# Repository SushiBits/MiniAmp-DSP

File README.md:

# MiniAmp DSP

Miniature Audio Amplifier with a DSP inside.

eUPID: `M2AUv3-AMP4268`

## Specifications

* Power input: DC 9-24V 6W, center positive barrel jack.
* Signal input: Unbalanced consumer line level, 3.5mm TRS jack.
* Outputs:
  * Left and Right speakers: balanced 6W class D output, screw terminals.
  * Center speaker: balanced 1W class AB output, screw terminals.
  * Subwoofer: Consumer line level, RCA coaxial.
  * Headphone: Unbalanced 6W class D output, 3.5mm TRS jack. The prescense of a
    headphone disables all other outputs.
* DSP: Analog Devices AD1701 SigmaDSP.

## Programming the DSP

This DSP is programmed using [Analog Devices SigmaStudio][1]. You need a USBi,
for example the [SigmaLink USBi][2], to program the devce.

[1]: https://www.analog.com/en/design-center/evaluation-hardware-and-software/software/ss_sigst_02.html
[2]: https://github.com/freeDSP/SigmaLink-USBi

## License & Contacts

Copyright &copy; 2019-2020 Max Chan. All rights reserved.

This project is licensed under [3-clause BSD license](LICENSE.md).

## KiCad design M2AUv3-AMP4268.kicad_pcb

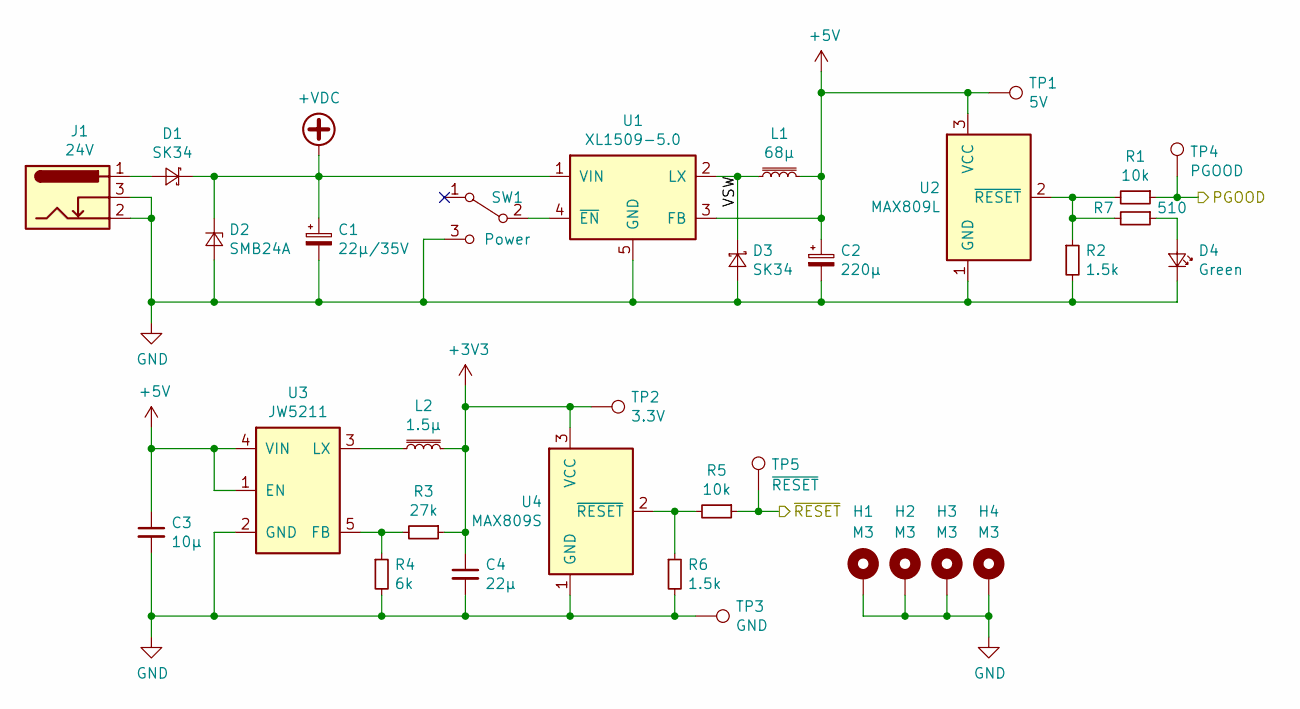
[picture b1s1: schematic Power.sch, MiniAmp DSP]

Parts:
C1: 22µ/35V; CP_Elec_6.3x5.4
C2: 220µ; CP_Elec_6.3x5.4
C3: 10µ; C_0805_2012Metric_Pad1.15x1.40mm_HandSolder
C4: 22µ; C_0805_2012Metric_Pad1.15x1.40mm_HandSolder
D1, D3: SK34; D_SMB
D2: SMB24A; D_SMB
D4: Green; LED_1206_3216Metric_Pad1.42x1.75mm_HandSolder
H1, H2, H3, H4: M3; MountingHole_3.2mm_M3_Pad_Via
J1: 24V; BarrelJack_Wuerth_6941xx301002
L1: 68µ; L_Taiyo-Yuden_NR-60xx_HandSoldering
L2: 1.5µ; L_0806_2016Metric_Pad1.15x1.80mm_HandSolder
R1, R5: 10k; R_0603_1608Metric_Pad1.05x0.95mm_HandSolder
R2, R6: 1.5k; R_0603_1608Metric_Pad1.05x0.95mm_HandSolder
R3: 27k; R_0603_1608Metric_Pad1.05x0.95mm_HandSolder
R4: 6k; R_0603_1608Metric_Pad1.05x0.95mm_HandSolder
R7: 510; R_0603_1608Metric_Pad1.05x0.95mm_HandSolder
SW1: Power; SW_SPDT_PCM12
TP1: 5V; TestPoint_Loop_D2.54mm_Drill1.5mm_Beaded
TP2: 3.3V; TestPoint_Loop_D2.54mm_Drill1.5mm_Beaded
TP3: GND; TestPoint_Loop_D2.54mm_Drill1.5mm_Beaded
TP4: PGOOD; TestPoint_Loop_D2.54mm_Drill1.5mm_Beaded
TP5: ~RESET; TestPoint_Loop_D2.54mm_Drill1.5mm_Beaded
U1: XL1509-5.0; SOIC-8_3.9x4.9mm_P1.27mm
U2: MAX809L; SOT-23
U3: JW5211; SOT-23-5
U4: MAX809S; SOT-23

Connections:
+3V3: C4.1, L2.2, R3.1, TP2.1, U4.3 (VCC); also elsewhere on the board
+5V: C2.1, C3.1, L1.2, TP1.1, U1.3 (FB), U2.3 (VCC), U3.1 (EN), U3.4 (VIN); also elsewhere on the board
+VDC: C1.1, D1.1 (K), D2.1 (K), U1.1 (VIN)
/DSP/~RESET: R5.1, TP5.1; also elsewhere on the board
/PGOOD: R1.1, TP4.1; also elsewhere on the board
/Power Delivery/VSW: D3.1 (K), L1.1, U1.2 (LX)
GND: C1.2, C2.2, C3.2, C4.2, D2.2 (A), D3.2 (A), D4.1 (K), H1.1, H2.1, H3.1, H4.1, J1.2, J1.3, R2.2, R4.2, R6.2, SW1.3 (C), TP3.1, U1.5 (GND), U1.6 (GND), U1.7 (GND), U1.8 (GND), U2.1 (GND), U3.2 (GND), U4.1 (GND); also elsewhere on the board
unnamed: D1.2 (A), J1.1
unnamed: D4.2 (A), R7.1
unnamed: L2.1, U3.3 (LX)
unnamed: R1.2, R2.1, R7.2, U2.2 (~RESET~)
unnamed: R3.2, R4.1, U3.5 (FB)
unnamed: R5.2, R6.1, U4.2 (~RESET~)
unnamed: SW1.2 (B), U1.4 (~EN)

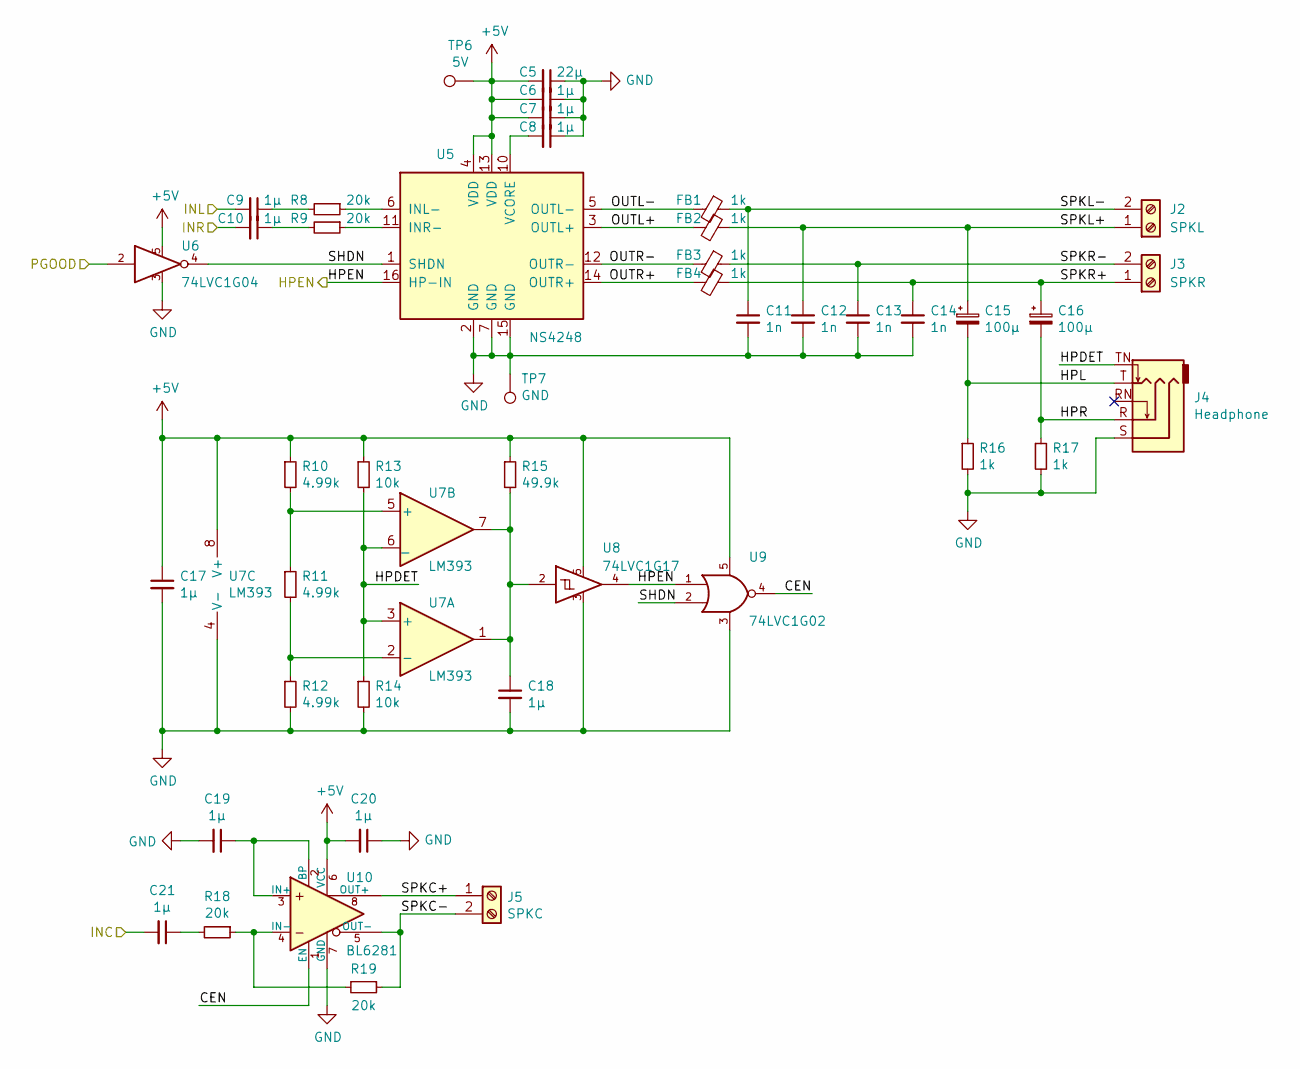
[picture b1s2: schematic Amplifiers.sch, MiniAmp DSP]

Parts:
C5: 22µ; C_0805_2012Metric_Pad1.15x1.40mm_HandSolder
C6, C7, C8, C9, C10, C17, C18, C19, C20, C21: 1µ; C_0603_1608Metric_Pad1.05x0.95mm_HandSolder
C11, C12, C13, C14: 1n; C_0603_1608Metric_Pad1.05x0.95mm_HandSolder
C15, C16: 100µ; CP_EIA-3528-21_Kemet-B_Pad1.50x2.35mm_HandSolder
FB1, FB2, FB3, FB4: 1k; L_0603_1608Metric_Pad1.05x0.95mm_HandSolder
J2: SPKL; TerminalBlock_Phoenix_MKDS-3-2-5.08_1x02_P5.08mm_Horizontal
J3: SPKR; TerminalBlock_Phoenix_MKDS-3-2-5.08_1x02_P5.08mm_Horizontal
J4: Headphone; Jack_3.5mm_Ledino_KB3SPRS_Horizontal
J5: SPKC; TerminalBlock_Phoenix_MKDS-3-2-5.08_1x02_P5.08mm_Horizontal
R8, R9, R18, R19: 20k; R_0603_1608Metric_Pad1.05x0.95mm_HandSolder
R10, R11, R12: 4.99k; R_0603_1608Metric_Pad1.05x0.95mm_HandSolder
R13, R14: 10k; R_0603_1608Metric_Pad1.05x0.95mm_HandSolder
R15: 49.9k; R_0603_1608Metric_Pad1.05x0.95mm_HandSolder
R16, R17: 1k; R_0603_1608Metric_Pad1.05x0.95mm_HandSolder
TP6: 5V; TestPoint_Loop_D2.54mm_Drill1.5mm_Beaded
TP7: GND; TestPoint_Loop_D2.54mm_Drill1.5mm_Beaded
U5: NS4248; SOIC-16_3.9x9.9mm_P1.27mm
U6: 74LVC1G04; SOT-23-5
U7: LM393; SOIC-8_3.9x4.9mm_P1.27mm
U8: 74LVC1G17; SOT-23-5
U9: 74LVC1G02; SOT-23-5
U10: BL6281; SOIC-8_3.9x4.9mm_P1.27mm

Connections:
+5V: C5.2, C6.2, C7.2, C17.1, C20.2, R10.1, R13.1, R15.1, TP6.1, U5.4 (VDD), U5.13 (VDD), U6.5, U7.8 (V+), U8.5, U9.5 (VCC), U10.6 (VCC); also elsewhere on the board
/Amplified Output/CEN: U9.4, U10.1 (EN)
/Amplified Output/HPDET: J4.TN, R13.2, R14.1, U7.3 (+), U7.6 (_)
/Amplified Output/HPEN: U5.16 (HP-IN), U8.4, U9.1; also elsewhere on the board
/Amplified Output/HPL: C15.2, J4.T, R16.1
/Amplified Output/HPR: C16.2, J4.R, R17.1
/Amplified Output/INC: C21.2; also elsewhere on the board
/Amplified Output/INL: C9.2; also elsewhere on the board
/Amplified Output/INR: C10.2; also elsewhere on the board
/Amplified Output/OUTL+: FB2.2, U5.3 (OUTL+)
/Amplified Output/OUTL-: FB1.2, U5.5 (OUTL-)
/Amplified Output/OUTR+: FB4.2, U5.14 (OUTR+)
/Amplified Output/OUTR-: FB3.2, U5.12 (OUTR-)
/Amplified Output/SHDN: U5.1 (SHDN), U6.4, U9.2
/Amplified Output/SPKC+: J5.1, U10.8 (OUT+)
/Amplified Output/SPKC-: J5.2, R19.1, U10.5 (OUT-)
/Amplified Output/SPKL+: C12.1, C15.1, FB2.1, J2.1
/Amplified Output/SPKL-: C11.1, FB1.1, J2.2
/Amplified Output/SPKR+: C14.1, C16.1, FB4.1, J3.1
/Amplified Output/SPKR-: C13.1, FB3.1, J3.2
/PGOOD: U6.2; also elsewhere on the board
GND: C5.1, C6.1, C7.1, C8.1, C11.2, C12.2, C13.2, C14.2, C17.2, C18.2, C19.2, C20.1, J4.S, R12.2, R14.2, R16.2, R17.2, TP7.1, U5.2 (GND), U5.7 (GND), U5.15 (GND), U6.3, U7.4 (V-), U8.3, U9.3 (GND), U10.7 (GND); also elsewhere on the board
unnamed: C8.2, U5.10 (VCORE)
unnamed: C9.1, R8.2
unnamed: C10.1, R9.2
unnamed: C18.1, R15.2, U7.1, U7.7, U8.2
unnamed: C19.1, U10.2 (BP), U10.3 (IN+)
unnamed: C21.1, R18.2
unnamed: R8.1, U5.6 (INL-)
unnamed: R9.1, U5.11 (INR-)
unnamed: R10.2, R11.1, U7.5 (+)
unnamed: R11.2, R12.1, U7.2 (-)
unnamed: R18.1, R19.2, U10.4 (IN-)

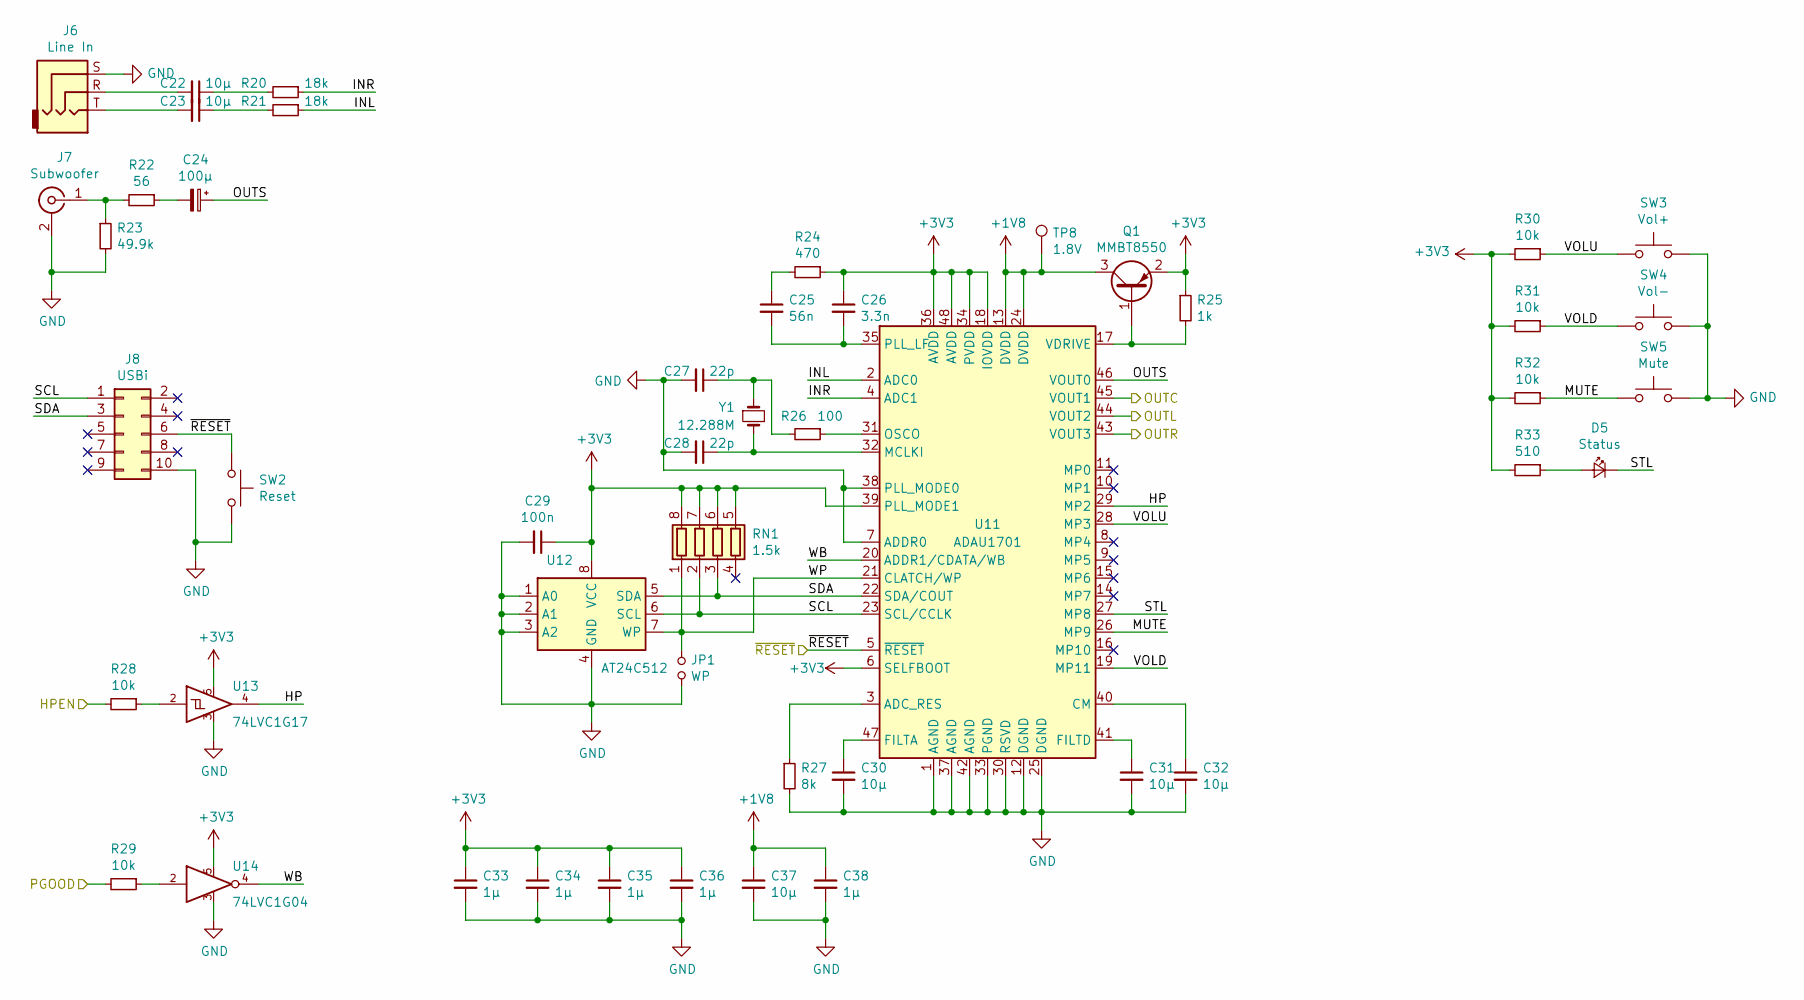
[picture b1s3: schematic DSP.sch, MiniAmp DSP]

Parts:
C22, C23, C30, C31, C32, C37: 10µ; C_0603_1608Metric_Pad1.05x0.95mm_HandSolder
C24: 100µ; CP_EIA-3528-21_Kemet-B_Pad1.50x2.35mm_HandSolder
C25: 56n; C_0603_1608Metric_Pad1.05x0.95mm_HandSolder
C26: 3.3n; C_0603_1608Metric_Pad1.05x0.95mm_HandSolder
C27, C28: 22p; C_0603_1608Metric_Pad1.05x0.95mm_HandSolder
C29: 100n; C_0603_1608Metric_Pad1.05x0.95mm_HandSolder
C33, C34, C35, C36, C38: 1µ; C_0603_1608Metric_Pad1.05x0.95mm_HandSolder
D5: Status; LED_1206_3216Metric_Pad1.42x1.75mm_HandSolder
J6: Line In; PJ3130
J7: Subwoofer; RCA
J8: USBi; IDC-Header_2x05_P2.54mm_Vertical
JP1: WP; PinHeader_2x01_P2.00mm_Vertical
Q1: MMBT8550; SOT-23
R20, R21: 18k; R_0603_1608Metric_Pad1.05x0.95mm_HandSolder
R22: 56; R_0603_1608Metric_Pad1.05x0.95mm_HandSolder
R23: 49.9k; R_0603_1608Metric_Pad1.05x0.95mm_HandSolder
R24: 470; R_0603_1608Metric_Pad1.05x0.95mm_HandSolder
R25: 1k; R_0603_1608Metric_Pad1.05x0.95mm_HandSolder
R26: 100; R_0603_1608Metric_Pad1.05x0.95mm_HandSolder
R27: 8k; R_0603_1608Metric_Pad1.05x0.95mm_HandSolder
R28, R29, R30, R31, R32: 10k; R_0603_1608Metric_Pad1.05x0.95mm_HandSolder
R33: 510; R_0603_1608Metric_Pad1.05x0.95mm_HandSolder
RN1: 1.5k; R_Array_Concave_4x0603
SW2: Reset; SW_SPST_1TS003B-0A
SW3: Vol+; SW_SPST_1TS003B-0A
SW4: Vol-; SW_SPST_1TS003B-0A
SW5: Mute; SW_SPST_1TS003B-0A
TP8: 1.8V; TestPoint_Loop_D2.54mm_Drill1.5mm_Beaded
U11: ADAU1701; LQFP-48_7x7mm_P0.5mm
U12: AT24C512; SOIC-8_3.9x4.9mm_P1.27mm
U13: 74LVC1G17; SOT-23-5
U14: 74LVC1G04; SOT-23-5
Y1: 12.288M; Crystal_SMD_5032-2Pin_5.0x3.2mm

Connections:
+1V8: C37.1, C38.1, Q1.3 (C), TP8.1, U11.13 (DVDD), U11.24 (DVDD)
+3V3: C26.1, C29.1, C33.1, C34.1, C35.1, C36.1, Q1.2 (E), R24.1, R25.1, R30.2, R31.2, R32.2, R33.2, RN1.5 (R4.2), RN1.6 (R3.2), RN1.7 (R2.2), RN1.8 (R1.2), U11.6 (SELFBOOT), U11.18 (IOVDD), U11.34 (PVDD), U11.36 (AVDD), U11.39 (PLL_MODE1), U11.48 (AVDD), U12.8 (VCC), U13.5, U14.5; also elsewhere on the board
/Amplified Output/HPEN: R28.2; also elsewhere on the board
/Amplified Output/INC: U11.45 (VOUT1); also elsewhere on the board
/Amplified Output/INL: U11.44 (VOUT2); also elsewhere on the board
/Amplified Output/INR: U11.43 (VOUT3); also elsewhere on the board
/DSP/HP: U11.29 (MP2), U13.4
/DSP/INL: R21.1, U11.2 (ADC0)
/DSP/INR: R20.1, U11.4 (ADC1)
/DSP/MUTE: R32.1, SW5.1, U11.26 (MP9)
/DSP/OUTS: C24.1, U11.46 (VOUT0)
/DSP/SCL: J8.1, RN1.2 (R2.1), U11.23 (SCL/CCLK), U12.6 (SCL)
/DSP/SDA: J8.3, RN1.3 (R3.1), U11.22 (SDA/COUT), U12.5 (SDA)
/DSP/STL: D5.1 (K), U11.27 (MP8)
/DSP/VOLD: R31.1, SW4.1, U11.19 (MP11)
/DSP/VOLU: R30.1, SW3.1, U11.28 (MP3)
/DSP/WB: U11.20 (ADDR1/CDATA/WB), U14.4
/DSP/WP: JP1.1, RN1.1 (R1.1), U11.21 (CLATCH/WP), U12.7 (WP)
/DSP/~RESET: J8.6, SW2.2, U11.5 (~RESET); also elsewhere on the board
/PGOOD: R29.2; also elsewhere on the board
GND: C27.2, C28.2, C29.2, C30.2, C31.2, C32.2, C33.2, C34.2, C35.2, C36.2, C37.2, C38.2, J6.S, J7.2 (Ext), J8.10, JP1.2, R23.2, R27.2, SW2.1, SW3.2, SW4.2, SW5.2, U11.1 (AGND), U11.7 (ADDR0), U11.12 (DGND), U11.25 (DGND), U11.30 (RSVD), U11.33 (PGND), U11.37 (AGND), U11.38 (PLL_MODE0), U11.42 (AGND), U12.1 (A0), U12.2 (A1), U12.3 (A2), U12.4 (GND), U13.3, U14.3; also elsewhere on the board
unnamed: C22.1, R20.2
unnamed: C22.2, J6.R
unnamed: C23.1, R21.2
unnamed: C23.2, J6.T
unnamed: C24.2, R22.1
unnamed: C25.1, R24.2
unnamed: C25.2, C26.2, U11.35 (PLL_LF)
unnamed: C27.1, R26.2, Y1.1
unnamed: C28.1, U11.32 (MCLKI), Y1.2
unnamed: C30.1, U11.47 (FILTA)
unnamed: C31.1, U11.41 (FILTD)
unnamed: C32.1, U11.40 (CM)
unnamed: D5.2 (A), R33.1
unnamed: J7.1 (In), R22.2, R23.1
unnamed: Q1.1 (B), R25.2, U11.17 (VDRIVE)
unnamed: R26.1, U11.31 (OSCO)
unnamed: R27.1, U11.3 (ADC_RES)
unnamed: R28.1, U13.2
unnamed: R29.1, U14.2

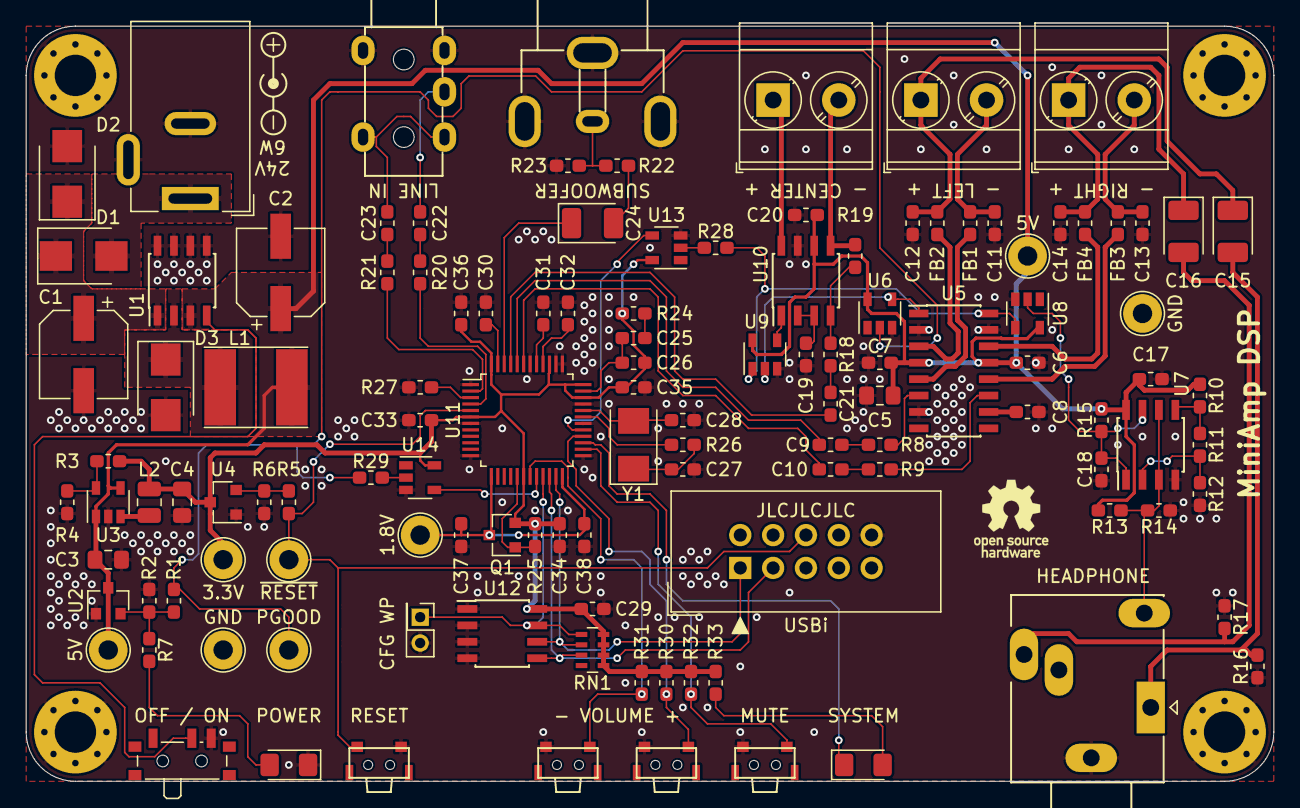
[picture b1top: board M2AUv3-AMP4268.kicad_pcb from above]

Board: 2 copper layers, 96.5 x 58.4 mm, 125 parts (0 on the bottom side), 76 nets.

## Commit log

2020-01-27 Initia commit
2020-01-27 Code dump: version 3 release 1
2020-01-27 Adding eUPID
2020-01-27 Noting that headphones disables other outputs.
2020-01-27 Adding instructions on programming the DSP
